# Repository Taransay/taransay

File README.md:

# Taransay home monitoring hardware and firmware
This is a series of wireless (433 MHz) electricity, gas, temperature and humidity monitors, electricity switches
and RGB(W) controllers and base station, with interoperability with [Home Assistant](https://www.home-assistant.io/). It uses low cost RF modules from HopeRF for intercommunication, avoiding the security
implications of having several seldomly-updated WiFi modules on your home network. The range is also
far greater.

The hardware and firmware designs are loosely based on those of the [emonTx](https://github.com/openenergymonitor/emontx3), [emonTH](https://github.com/openenergymonitor/emonth2) (both [OpenEnergyMonitor](http://openenergymonitor.com/)) and [Moteino](https://lowpowerlab.com/guide/moteino/) (LowPowerLab).

The firmware is designed to talk to Home Assistant via the Taransay base station, which is a small
transceiver that plugs into a Raspberry Pi or similar and talks to an instance of [Taransay
Data Forwarder](https://github.com/Taransay/taransayhub) over serial. This way, you just need to
keep your Raspberry Pi updated and not several distributed devices.

## Status
The hardware and firmware all works, though there are few instructions for getting it all to work,
so if you happen to want to use any of this it's best to get in touch.

## Credits
Sean Leavey <https://github.com/SeanDS>

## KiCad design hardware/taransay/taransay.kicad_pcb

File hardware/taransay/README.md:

Taransay
========

Arduino-compatible RF transceiver board.

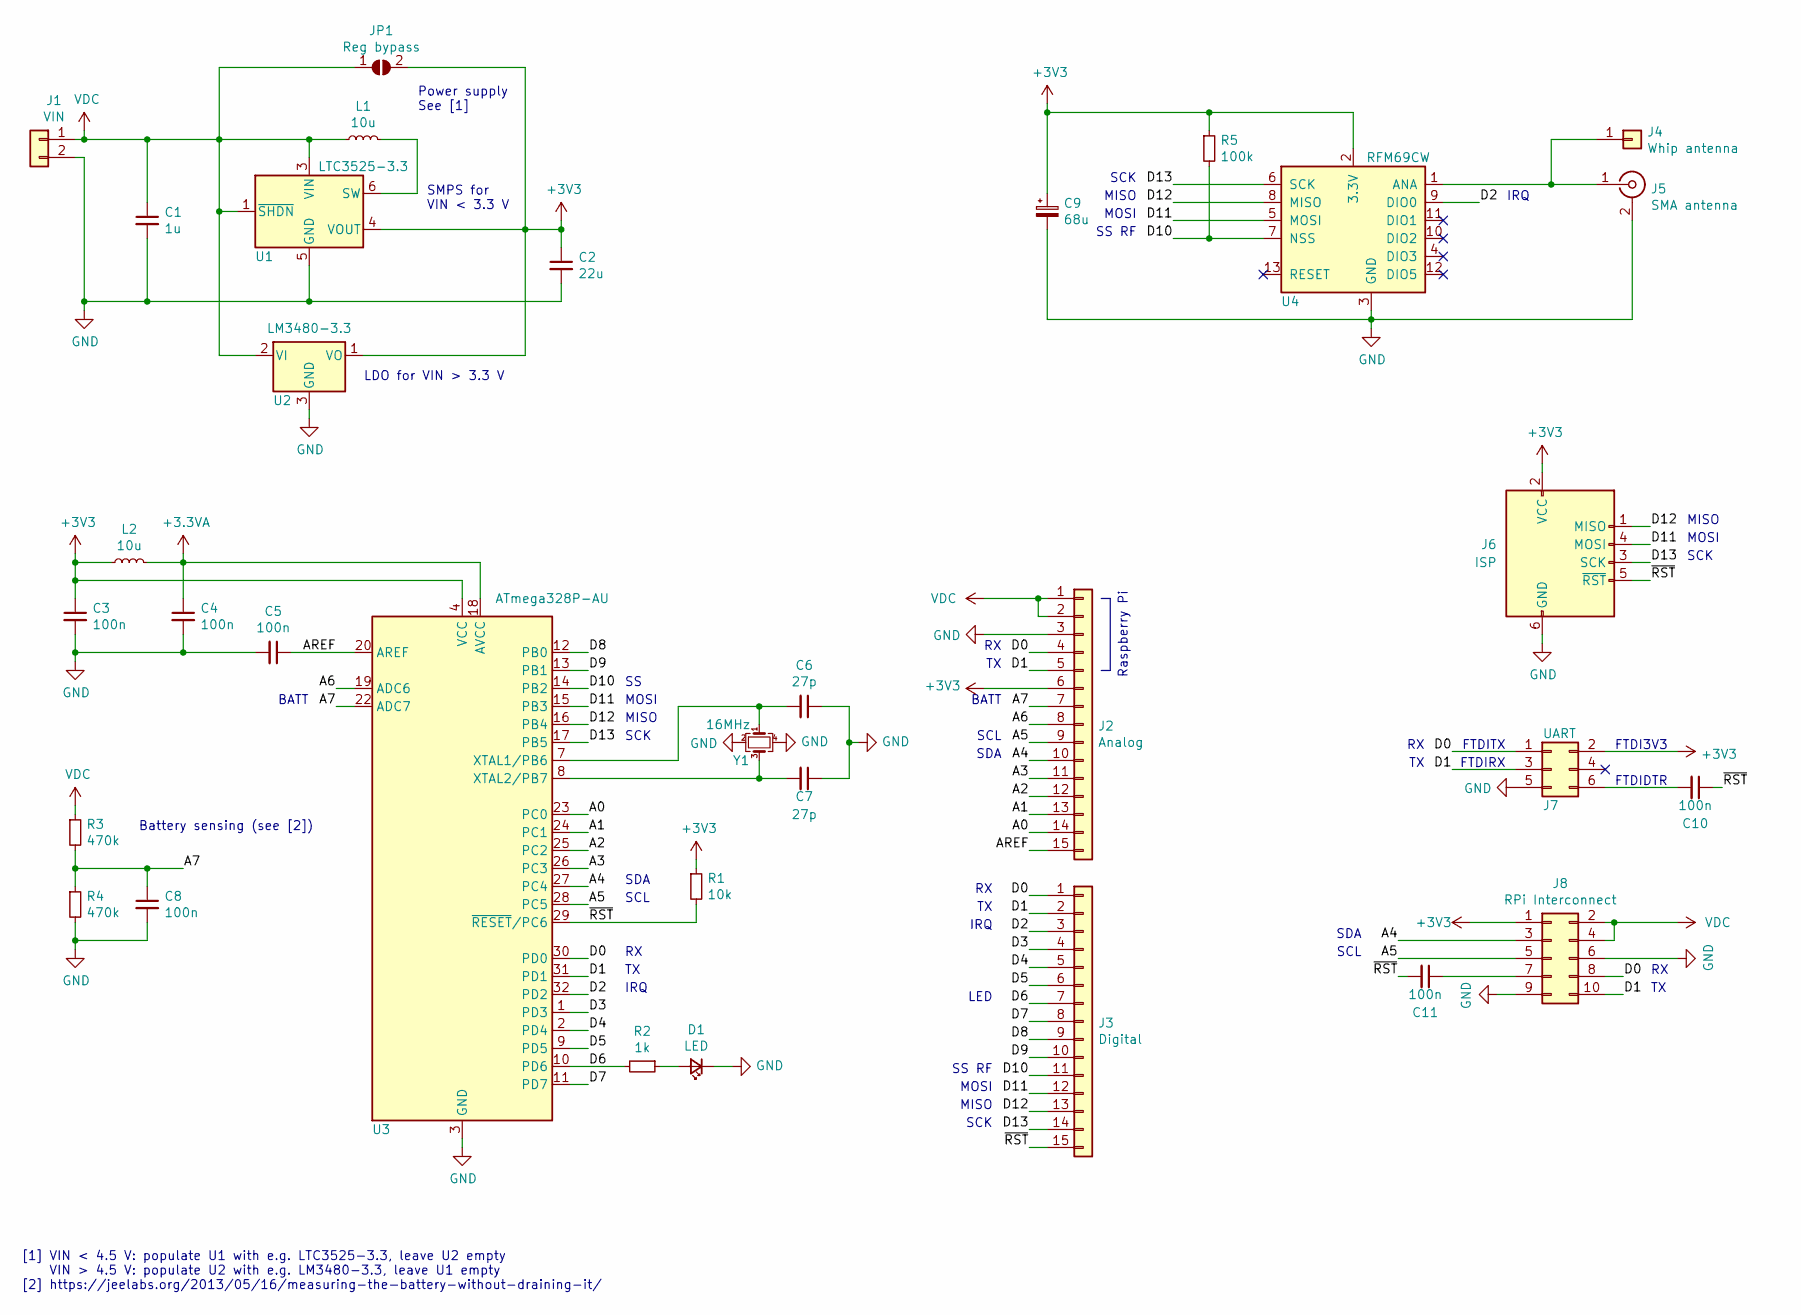
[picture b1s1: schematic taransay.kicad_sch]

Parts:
C1: 1u; C_0805_2012Metric; MPN1 C0805C105K4RACTU
C2: 22u; C_0805_2012Metric; MPN1 C0805C220J5GACTU
C3, C4, C5, C8, C10, C11: 100n; C_0805_2012Metric
C6, C7: 27p; C_0603_1608Metric
C9: 68u; CP_Radial_D6.3mm_P2.50mm
D1: LED; LED_0805_2012Metric_Pad1.15x1.40mm_HandSolder; MPN1 LG R971
J1: VIN; SolderWire-0.75sqmm_1x02_P4.8mm_D1.25mm_OD2.3mm
J2: Analog; PinSocket_1x15_P2.54mm_Vertical
J3: Digital; PinSocket_1x15_P2.54mm_Vertical
J4: Whip antenna; SolderWire-0.25sqmm_1x01_D0.65mm_OD1.7mm
J5: SMA antenna; SMA_Molex_73251-1153_EdgeMount_Horizontal; MPN1 73251-1150
J6: ISP; PinHeader_2x03_P2.54mm_Vertical; MPN1 251-8137
J7: UART; PinHeader_2x03_P2.54mm_Vertical; MPN1 251-8121
J8: RPi Interconnect; PinSocket_2x05_P2.54mm_Vertical; MPN1 215307-5
JP1: Reg bypass; SolderJumper-2_P1.3mm_Open_RoundedPad1.0x1.5mm
L1, L2: 10u; L_1210_3225Metric_Pad1.42x2.65mm_HandSolder; MPN1 LQH32CN100K53L
R1: 10k; R_0805_2012Metric
R2: 1k; R_0805_2012Metric
R3, R4: 470k; R_0805_2012Metric
R5: 100k; R_0805_2012Metric
U1: LTC3525-3.3; SOT-363_SC-70-6; MPN1 LTC3525ESC6-3.3#TRMPBF
U2: LM3480-3.3; SOT-23
U3: ATmega328P-AU; TQFP-32_7x7mm_P0.8mm
U4: RFM69CW; HOPERF_RFM69CW
Y1: 16MHz; Crystal_SMD_Abracon_ABM8G-4Pin_3.2x2.5mm; MPN1 ABM8-16.000MHZ-7-1-U-T

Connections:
+3.3VA: C4.1, L2.2, U3.18 (AVCC)
+3V3: C2.1, C3.1, C9.1, J2.6, J6.2 (VCC), J7.2, J8.1, JP1.2 (B), L2.1, R1.1, R5.1, U1.4 (VOUT), U2.1 (VO), U3.4 (VCC), U3.6 (VCC), U4.2 (3.3V)
/A0: J2.14, U3.23 (PC0)
/A1: J2.13, U3.24 (PC1)
/A2: J2.12, U3.25 (PC2)
/A3: J2.11, U3.26 (PC3)
/A4: J2.10, J8.3, U3.27 (PC4)
/A5: J2.9, J8.5, U3.28 (PC5)
/A6: J2.8, U3.19 (ADC6)
/A7: C8.1, J2.7, R3.2, R4.1, U3.22 (ADC7)
/AREF: C5.1, J2.15, U3.20 (AREF)
/D0: J2.4, J3.1, J7.1, J8.8, U3.30 (PD0)
/D1: J2.5, J3.2, J7.3, J8.10, U3.31 (PD1)
/D2: J3.3, U3.32 (PD2), U4.9 (DIO0)
/D3: J3.4, U3.1 (PD3)
/D4: J3.5, U3.2 (PD4)
/D5: J3.6, U3.9 (PD5)
/D6: J3.7, R2.2, U3.10 (PD6)
/D7: J3.8, U3.11 (PD7)
/D8: J3.9, U3.12 (PB0)
/D9: J3.10, U3.13 (PB1)
/D10: J3.11, R5.2, U3.14 (PB2), U4.7 (NSS)
/D11: J3.12, J6.4 (MOSI), U3.15 (PB3), U4.5 (MOSI)
/D12: J3.13, J6.1 (MISO), U3.16 (PB4), U4.8 (MISO)
/D13: J3.14, J6.3 (SCK), U3.17 (PB5), U4.6 (SCK)
/~RST: C10.1, C11.2, J3.15, J6.5 (~RST), R1.2, U3.29 (~RESET/PC6)
GND: C1.2, C2.2, C3.2, C4.2, C5.2, C6.1, C7.1, C8.2, C9.2, D1.1 (K), J1.2, J2.3, J5.2 (Ext), J6.6 (GND), J7.5, J8.6, J8.9, R4.2, U1.2 (GND), U1.5 (GND), U2.3 (GND), U3.3 (GND), U3.5 (GND), U3.21 (GND), U4.3 (GND), U4.14 (GND), Y1.2, Y1.4
unnamed: C6.2, U3.7 (XTAL1/PB6), Y1.1
unnamed: C7.2, U3.8 (XTAL2/PB7), Y1.3
unnamed: C10.2, J7.6
unnamed: C11.1, J8.7
unnamed: D1.2 (A), R2.1
unnamed: J4.1, J5.1 (In), U4.1 (ANA)
unnamed: L1.2, U1.6 (SW)
VDC: C1.1, J1.1, J2.1, J2.2, J8.2, J8.4, JP1.1 (A), L1.1, R3.1, U1.1 (~SHDN), U1.3 (VIN), U2.2 (VI)

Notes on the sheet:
LED
MISO
FTDI3V3
FTDIDTR
IRQ
SCL
SCK
MOSI
BATT
[1] VIN < 4.5 V: populate U1 with e.g. LTC3525-3.3, leave U2 empty VIN > 4.5 V: populate U2 with e.g. LM3480-3.3, leave U1 empty [2] https://jeelabs.org/2013/05/16/measuring-the-battery-without-draining-it/
SDA
LDO for VIN > 3.3 V
FTDITX
Battery sensing (see [2])
FTDIRX
SS RF
SMPS for VIN < 3.3 V
Power supply See [1]
Raspberry Pi

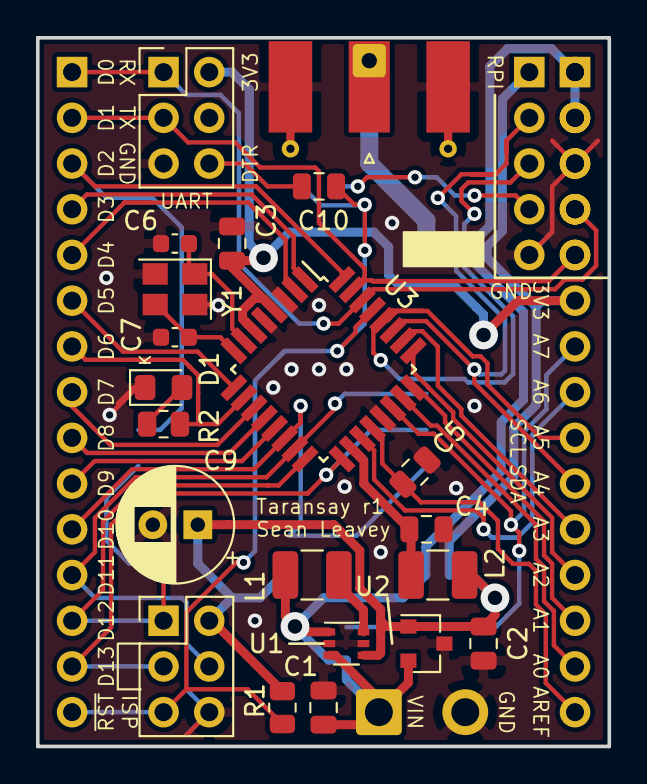
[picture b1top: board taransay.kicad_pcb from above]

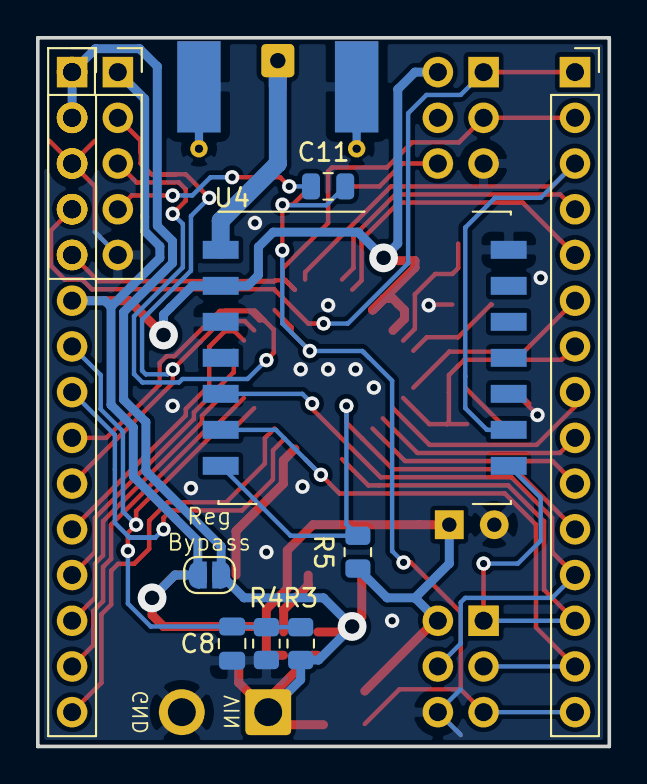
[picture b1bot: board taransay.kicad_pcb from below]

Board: 2 copper layers, 31.8 x 39.4 mm, 33 parts (10 on the bottom side), 35 nets.

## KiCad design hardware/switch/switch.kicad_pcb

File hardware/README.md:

Changes from emonTx V3.4 / emonTH V2.0
======================================

- Various component tweaks: different models, mainly
- Removed 3/4 current sensors
- Added Si7020/Si7021 temperature/humidity probe from emonTH V2
  - Reused ADC4 and ADC5 for SDA/SCL I2C bus to communicate with Si7020
  - Changed DS18B20 data pin from D5 to PC2 (ADC2) amd power pin from ADC5 to PC3 (ADC3)
- Removed ESP UART socket
- Explicitly implemented RFM69CW instead of (pin compatible) RFM12B
- Split pulse and temperature monitor ports into separate ports
  - Made PD4 the pulse power pin
- Changed pulse and temperature sockets from RJ45 to Molex Nano-Fit
- Removed AC-AC input
- Removed USB socket

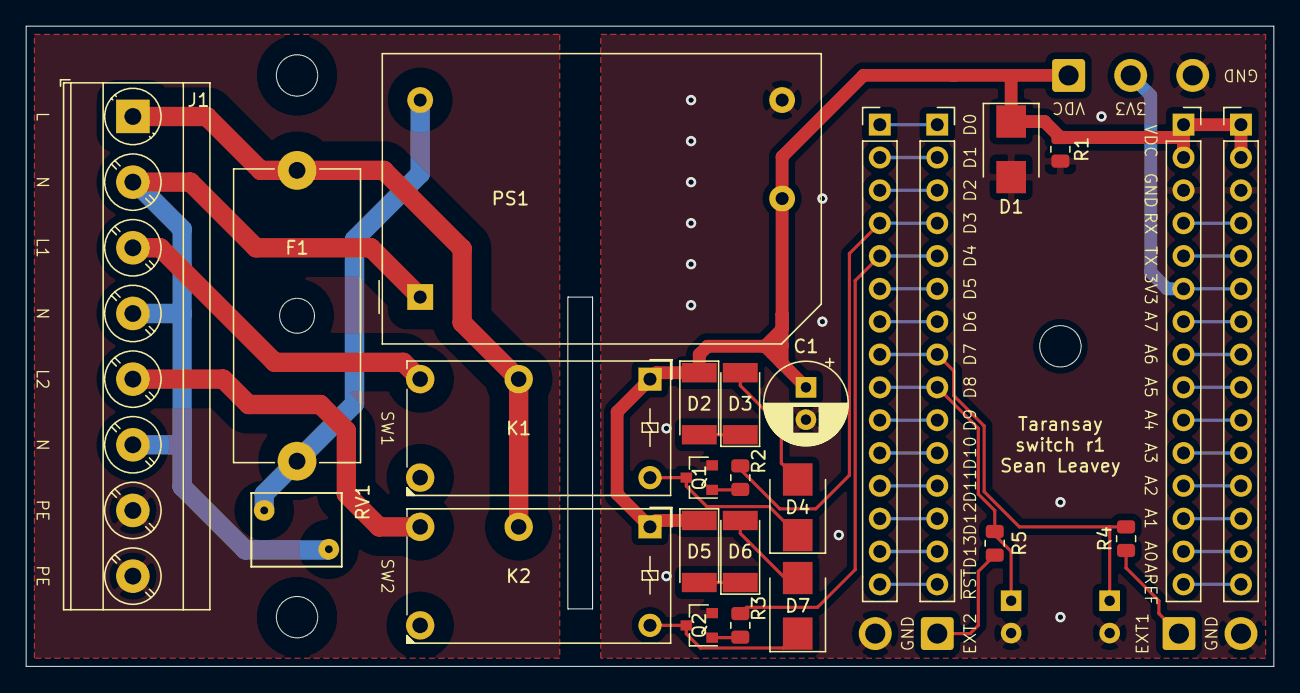
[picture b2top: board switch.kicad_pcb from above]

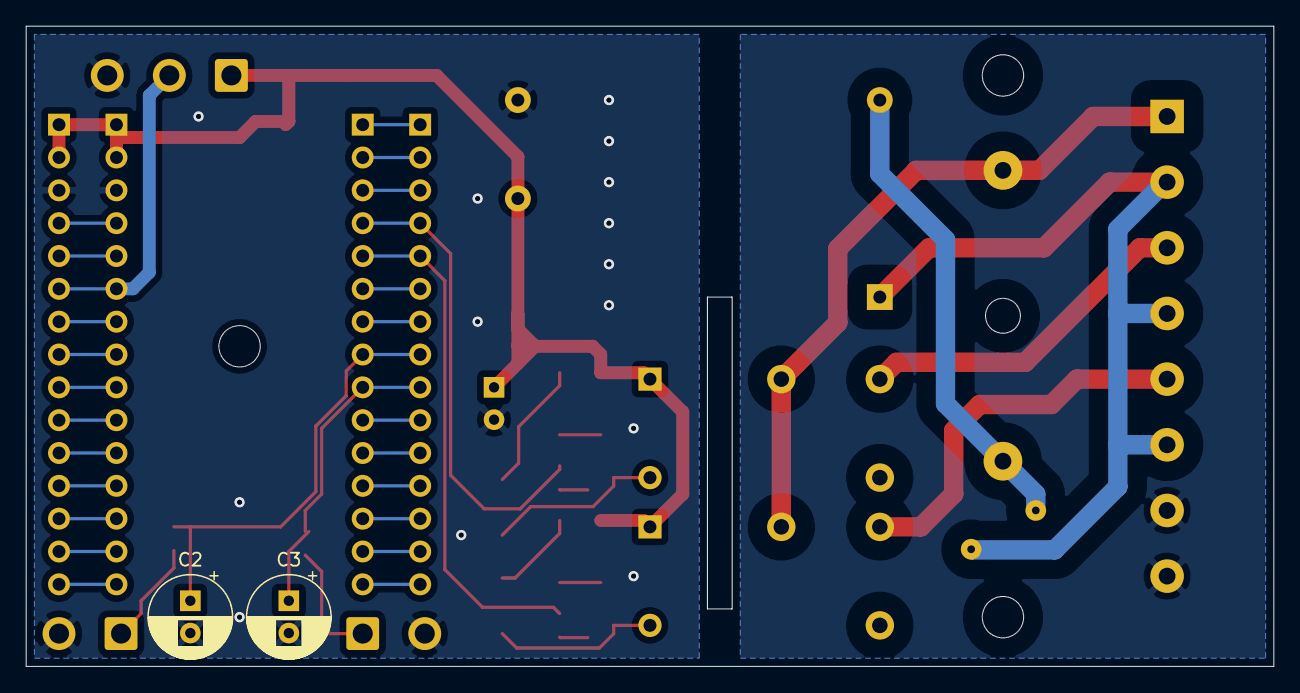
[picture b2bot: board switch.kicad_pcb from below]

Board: 2 copper layers, 96.5 x 49.5 mm, 33 parts (2 on the bottom side), 43 nets.

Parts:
C1, C2, C3: 68u; CP_Radial_D6.3mm_P2.50mm
D1, D4, D7: SMBJ7.0A; D_SMB
D2, D3, D5, D6: SM4007; D_MELF
F1: Fuse; Fuseholder_Cylinder-5x20mm_Schurter_0031_8201_Horizontal_Op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
H1, H2, H3: MountingHole; MountingHole_3.2mm_M3
J1: Power; TerminalBlock_Phoenix_MKDS-3-8-5.08_1x08_P5.08mm_Horizontal
J2: DC; SolderWire-0.75sqmm_1x03_P4.8mm_D1.25mm_OD2.3mm
J3: External button 1; SolderWire-0.75sqmm_1x02_P4.8mm_D1.25mm_OD2.3mm
J4: External button 2; SolderWire-0.75sqmm_1x02_P4.8mm_D1.25mm_OD2.3mm
J5: Analog; PinHeader_1x15_P2.54mm_Vertical
J6: Digital; PinHeader_1x15_P2.54mm_Vertical
J7: Analog breakout; PinSocket_1x15_P2.54mm_Vertical
J8: Digital breakout; PinSocket_1x15_P2.54mm_Vertical
K1, K2: FINDER-32.21-x000; Relay_SPDT_Finder_32.21-x000
PS1: RAC01-05SGB; Converter_ACDC_RECOM_RAC01-xxSGB_THT
Q1, Q2: MMBT2222AL; SOT-23
R1: NP; R_0805_2012Metric
R2, R3: 3k01; R_0805_2012Metric
R4, R5: 1k; R_0805_2012Metric
RV1: Varistor; RV_Disc_D7mm_W5.7mm_P5mm

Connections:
+3V3: J2.2, J5.6, J7.6
/A0: J5.14, J7.14
/A1: J5.13, J7.13
/A2: J5.12, J7.12
/A3: J5.11, J7.11
/A4: J5.10, J7.10
/A5: J5.9, J7.9
/A6: J5.8, J7.8
/A7: J5.7, J7.7
/AREF: J5.15, J7.15
/D0: J5.4, J6.1, J7.4, J8.1
/D1: J5.5, J6.2, J7.5, J8.2
/D2: J6.3, J8.3
/D3: J6.4, J8.4, R2.2
/D4: J6.5, J8.5, R3.2
/D5: J6.6, J8.6
/D6: J6.7, J8.7
/D7: C2.1, J6.8, J8.8, R4.2
/D8: C3.1, J6.9, J8.9, R5.2
/D9: J6.10, J8.10
/D10: J6.11, J8.11
/D11: J6.12, J8.12
/D12: J6.13, J8.13
/D13: J6.14, J8.14
/~RST: J6.15, J8.15
Earth_Protective: J1.7, J1.8
GND: C1.2, C2.2, C3.2, D1.2, J2.3, J3.2, J4.2, J5.3, J7.3, PS1.3, Q1.2, Q2.2, R1.2
unnamed: D2.2, D3.1
unnamed: D3.2, D4.2
unnamed: D4.1, K1.A2, Q1.3
unnamed: D5.2, D6.1
unnamed: D6.2, D7.2
unnamed: D7.1, K2.A2, Q2.3
unnamed: F1.1, PS1.2, RV1.1
unnamed: F1.2, J1.1, K1.11, K2.11
unnamed: J1.2, J1.4, J1.6, PS1.1, RV1.2
unnamed: J1.3, K1.14
unnamed: J1.5, K2.14
unnamed: J3.1, R4.1
unnamed: J4.1, R5.1
unnamed: Q1.1, R2.1
unnamed: Q2.1, R3.1
VDC: C1.1, D1.1, D2.1, D5.1, J2.1, J5.1, J5.2, J7.1, J7.2, K1.A1, K2.A1, PS1.4, R1.1

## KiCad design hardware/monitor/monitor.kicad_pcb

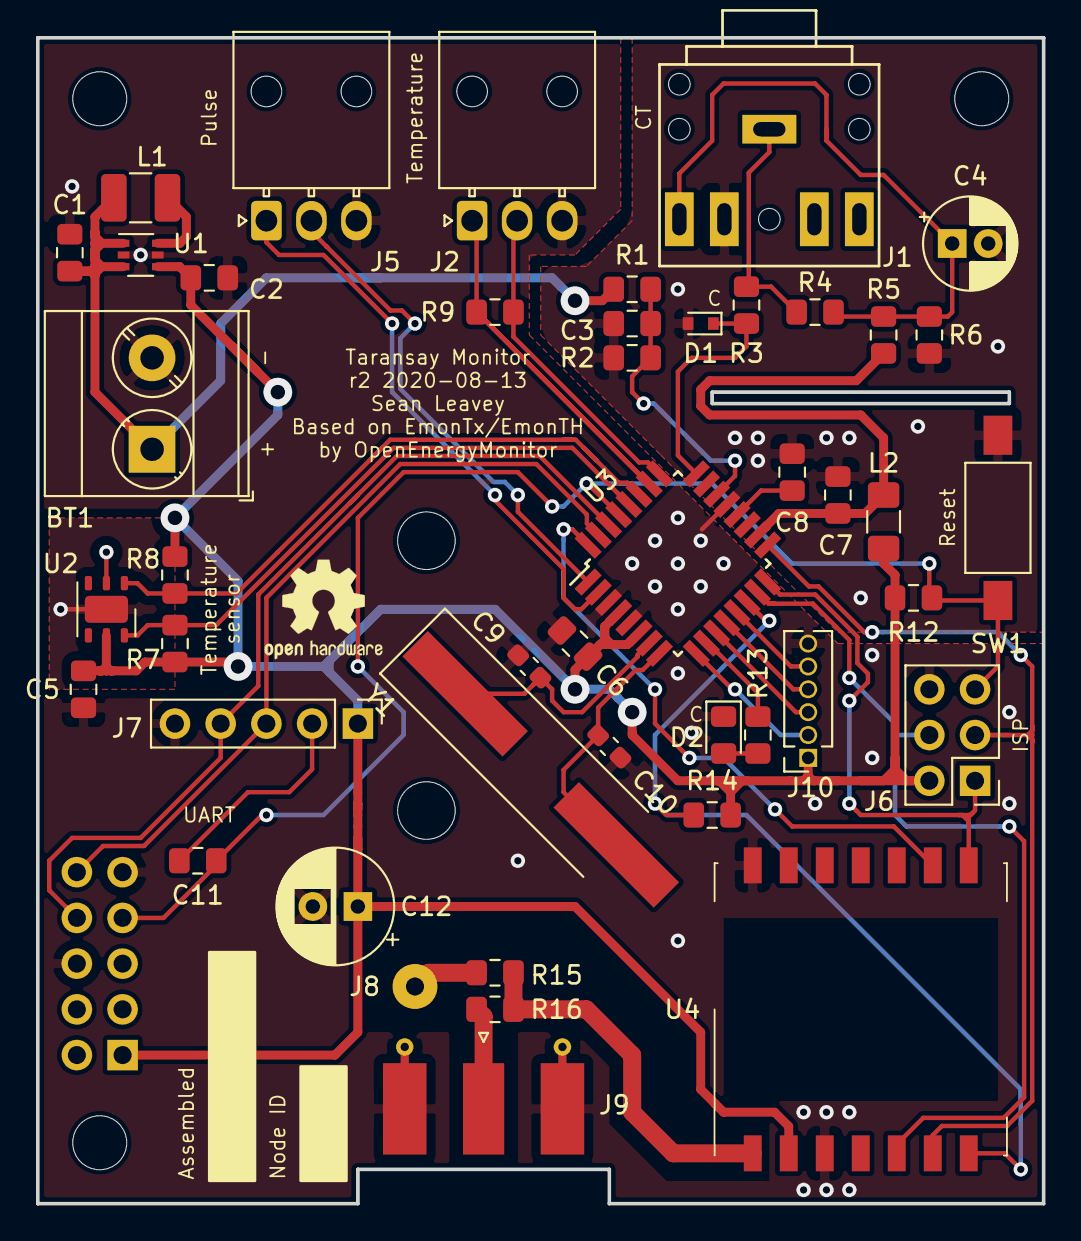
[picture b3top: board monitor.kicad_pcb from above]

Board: 2 copper layers, 55.9 x 64.8 mm, 52 parts (1 on the bottom side), 36 nets.

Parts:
BT1: Battery; TerminalBlock_Phoenix_MKDS-3-2-5.08_1x02_P5.08mm_Horizontal
C1: 1u; C_0805_2012Metric_Pad1.15x1.40mm_HandSolder
C2: 22u; C_0805_2012Metric_Pad1.15x1.40mm_HandSolder
C3: NP; C_0805_2012Metric_Pad1.15x1.40mm_HandSolder
C4: 10u; CP_Radial_D5.0mm_P2.00mm
C5, C6, C7, C8, C11: 100n; C_0805_2012Metric_Pad1.15x1.40mm_HandSolder
C9, C10: 26p; C_0603_1608Metric_Pad1.05x0.95mm_HandSolder
C12: 68u; CP_Radial_D6.3mm_P2.50mm
D1: ESD5Z3.3T1G; D_SOD-523
D2: LED; LED_0805_2012Metric_Pad1.15x1.40mm_HandSolder
H1: Mount 1; MountingHole_3mm
H2: Mount 2; MountingHole_3mm
H3: Mount 3; MountingHole_3mm
H5: Battery Mount 1; MountingHole_3.2mm_M3
H6: Battery Mount 2; MountingHole_3.2mm_M3
J1: CT; StereoJack_3.5mm_Switch_Cliff_JY039-5P_Horizontal
J2: T1; Molex_Nano-Fit_105313-xx03_1x03_P2.50mm_Horizontal
J3: RPi Interconnect; PinSocket_2x05_P2.54mm_Vertical
J5: Pulse; Molex_Nano-Fit_105313-xx03_1x03_P2.50mm_Horizontal
J6: ISP; PinHeader_2x03_P2.54mm_Vertical
J7: UART; PinHeader_1x05_P2.54mm_Vertical
J8: Whip antenna; SolderWirePad_1x01_Drill1mm
J9: SMA antenna; SMA_Molex_73251-1153_EdgeMount_Horizontal
J10: Spare; PinSocket_1x06_P1.27mm_Vertical
L1: 10u; L_1210_3225Metric_Pad1.42x2.65mm_HandSolder
L2: 10u; L_1206_3216Metric_Pad1.42x1.75mm_HandSolder
LOGO1: Logo; OSHW-Logo2_7.3x6mm_SilkScreen
R1, R2: 470k; R_0805_2012Metric_Pad1.15x1.40mm_HandSolder
R3, R13: 1k; R_0805_2012Metric_Pad1.15x1.40mm_HandSolder
R4: 22R/0.1%; R_0805_2012Metric_Pad1.15x1.40mm_HandSolder
R5, R6: 470k/0.1%; R_0805_2012Metric_Pad1.15x1.40mm_HandSolder
R7, R8, R9: 4k7; R_0805_2012Metric_Pad1.15x1.40mm_HandSolder
R12: 10k; R_0805_2012Metric_Pad1.15x1.40mm_HandSolder
R14: 100k; R_0805_2012Metric_Pad1.15x1.40mm_HandSolder
R15, R16: 0R; R_0805_2012Metric_Pad1.15x1.40mm_HandSolder
SW1: Reset; SW_SPST_FSMSM
U1: LTC3525-3.3; SOT-363_SC-70-6
U2: Si7020-A20; DFN-6-1EP_3x3mm_P1mm_EP1.5x2.4mm
U3: ATmega328P-AU; TQFP-32_7x7mm_P0.8mm
U4: RFM69CW; HOPERF_RFM69CW
Y1: 16MHz; Crystal_SMD_HC49-SD_HandSoldering

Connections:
+3.3VA: C7.1, L2.1, R5.1, U3.18
+3V3: C2.1, C5.1, C6.1, C12.1, J3.1, J6.2, J7.1, J10.1, L2.2, R7.1, R8.1, R12.1, R14.1, U1.4, U2.5, U3.4, U3.6, U4.2
+BATT: BT1.1, C1.1, L1.1, R1.1, U1.1, U1.3
/Microcontroller/BATT_MON: C3.1, R1.2, R2.1, U3.22
/Microcontroller/CT_SIGNAL: D1.1, R3.1, U3.24
/Microcontroller/D5: J10.2, U3.9
/Microcontroller/D7: J10.3, U3.11
/Microcontroller/D8: J10.4, U3.12
/Microcontroller/D9: J10.5, U3.13
/Microcontroller/DS_POWER: J2.1, R9.1, U3.26
/Microcontroller/DS_SIGNAL: J2.2, R9.2, U3.25
/Microcontroller/MISO: J6.1, U3.16, U4.8
/Microcontroller/MOSI: J6.4, U3.15, U4.5
/Microcontroller/PULSE_IRQ: J5.2, U3.1
/Microcontroller/PULSE_POWER: J5.1, U3.2
/Microcontroller/RF_IRQ: U3.32, U4.9
/Microcontroller/RF_SS: R14.2, U3.14, U4.7
/Microcontroller/RX: J3.8, J7.4, U3.30
/Microcontroller/Reset: C11.2, J3.7, J6.5, R12.2, SW1.1, U3.29
/Microcontroller/SCK: J6.3, U3.17, U4.6
/Microcontroller/SCL: R7.2, U2.6, U3.28
/Microcontroller/SDA: R8.2, U2.1, U3.27
/Microcontroller/TX: J3.10, J7.3, U3.31
GND: BT1.2, C1.2, C2.2, C3.2, C4.2, C5.2, C6.2, C7.2, C8.2, C9.1, C10.1, C12.2, D1.2, D2.1, J1.4, J2.3, J3.6, J3.9, J5.3, J6.6, J7.5, J9.2, J10.6, R2.2, R6.2, SW1.2, U1.2, U1.5, U2.2, U3.3, U3.5, U3.21, U4.3, U4.14
unnamed: C4.1, J1.5, R4.2, R5.2, R6.1
unnamed: C8.1, U3.20
unnamed: C9.2, U3.7, Y1.1
unnamed: C10.2, U3.8, Y1.2
unnamed: C11.1, J7.2
unnamed: D2.2, R13.1
unnamed: J1.1, R3.2, R4.1
unnamed: J8.1, R15.1
unnamed: J9.1, R16.1
unnamed: L1.2, U1.6
unnamed: R13.2, U3.10
unnamed: R15.2, R16.2, U4.1

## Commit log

2018-09-30 Add r1 hardware
2018-11-11 Update modules
2018-11-11 Remove libraries
2018-11-11 Working example firmware
2018-11-12 Add current transducer support
2018-11-12 Fix temperature readout
2018-11-12 Set default temperature when sensor not detected
2018-11-17 Fix battery monitor code
2019-02-19 Add temperature/humidity node firmware
2019-08-12 Add firmware
2019-08-16 Version with CurrentTransformer library (https://github.com/JChristensen/CurrentTransformer)
2019-08-16 reverted to use emonTx CT code
2019-11-04 Update flash instructions
2020-08-13 Hardware revision 2
2020-09-27 Add semicolon before non-data serial messages
2021-11-17 Move Taransay Monitor to subdirectory; add BOM
2021-11-17 Add Taransay transceiver
2021-11-17 Add hardware lib table
2021-11-17 Add hardware symbol lib table
2021-11-17 Add Taransay switch
2021-11-17 Update gitignore
2021-11-17 Remove JLCPCB silkscreen text
2021-11-17 Fix capacitor value
2022-04-30 Taransay RGBW firmware and schematic as used for large matchstick light
2022-11-02 Taransay RGB v1.0.0
2022-11-02 Replace LED library with FastLED, which allows dithering to achieve lower brightnesses
2022-11-27 Update sketches to use RFM69 library instead of JeeLib; add new examples
2022-11-27 Clean up unused files
2022-11-27 Update switch hardware
2022-11-27 Update Taransay board to Kicad 6
2022-12-31 Taransay CT firmware v1.2.0
2022-12-31 Fix Makefile
2023-02-19 Fix RGBW on/off via HomeAssistant app bug
2023-10-07 Remove several debug behaviours from non-debug run; use LowPowerLab sleep function instead of custom one; general restructuring
2023-10-07 Update KiCad project files to v7
